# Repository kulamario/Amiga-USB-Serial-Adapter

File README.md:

# Amiga-USB-Serial-Adapter

A simple interface that allows you to connect your Amiga to any PC via a terminal

RS232 and TTL operation possible switched with jumpers

No need drivers just connect via USB to PC

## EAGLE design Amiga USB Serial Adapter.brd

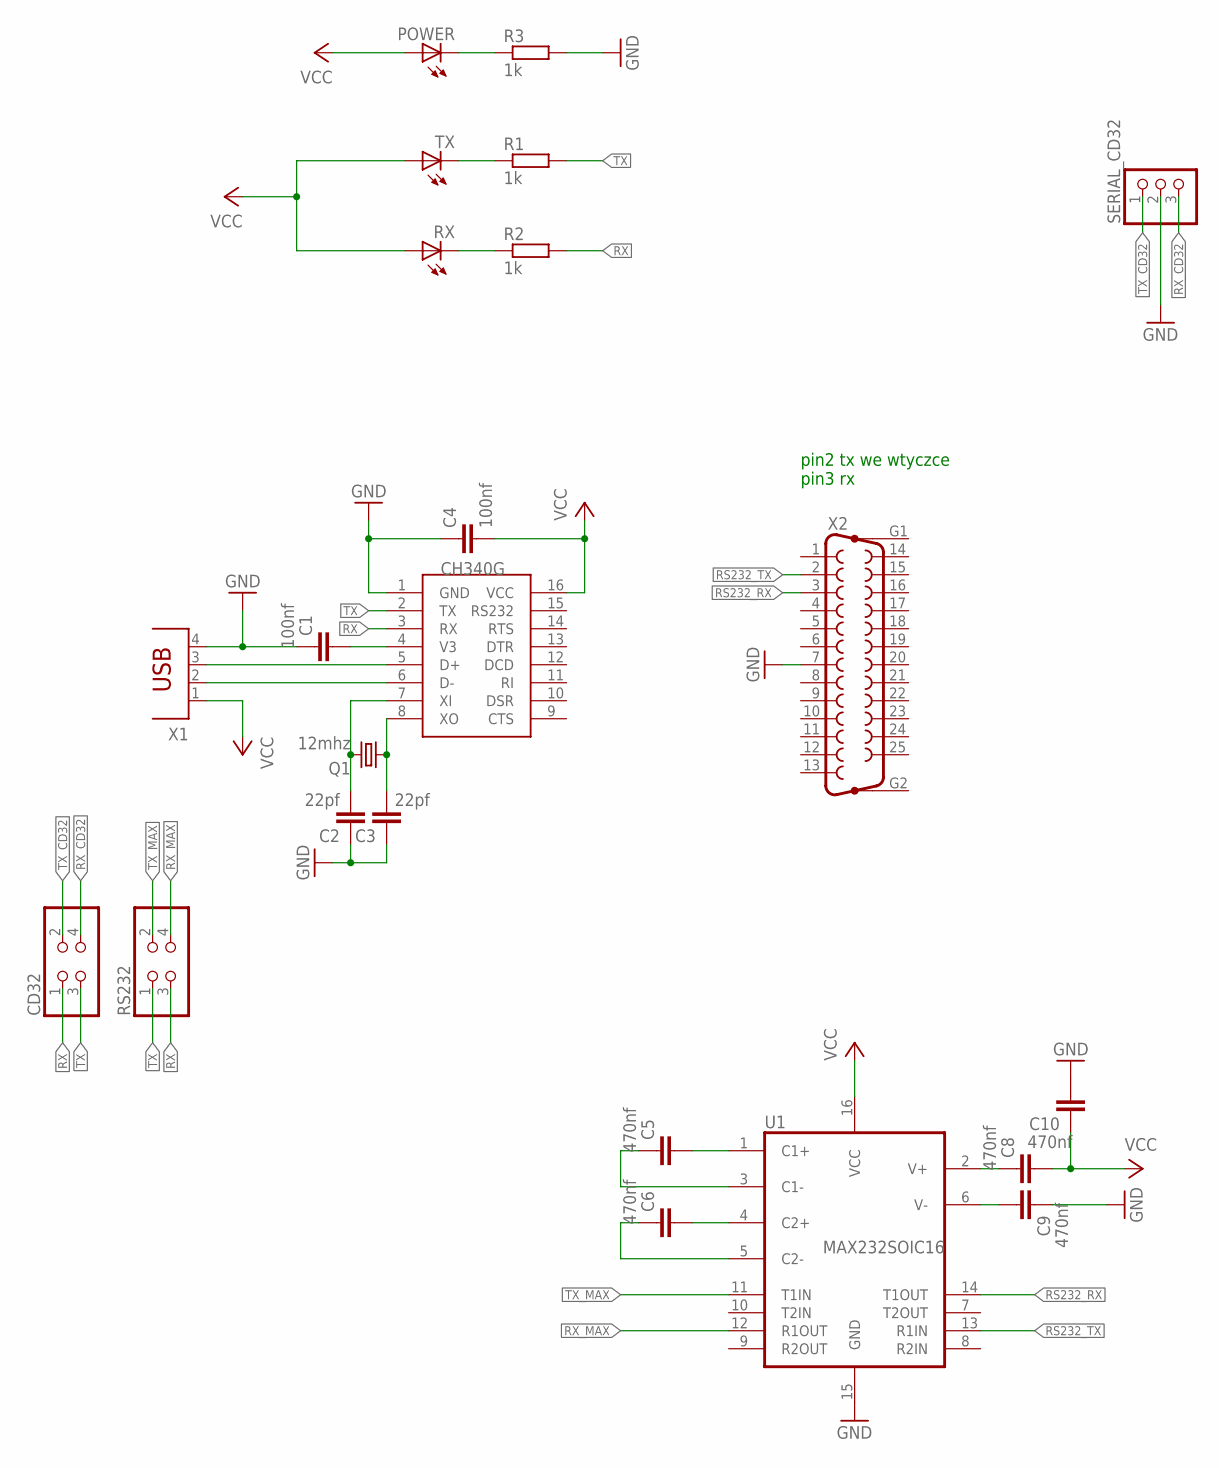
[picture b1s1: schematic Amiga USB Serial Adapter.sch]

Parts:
C1, C4: 100nf; C0805
C2, C3: 22pf; C0805
C5, C6, C8, C9, C10: 470nf; C0805
CD32: PINHD-2X2; 2X02
POWER: LEDCHIPLED_0805; CHIPLED_0805
Q1: 12mhz; HC49U-V
R1, R2, R3: 1k; R0805
RS232: PINHD-2X2; 2X02
RX: LEDCHIPLED_0805; CHIPLED_0805
SERIAL_CD32: PINHD-1X3; 1X03
TX: LEDCHIPLED_0805; CHIPLED_0805
U1: MAX232SOIC16; SO016
U$1: CH340G; SOIC16
X1: PN61729
X2: F25HP

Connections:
GND: C1.1, C2.1, C3.1, C4.1, C9.1, C10.2, R3.2, SERIAL_CD32.2, U1.15 (GND), U$1.1 (GND), X1.4, X2.7
unnamed: U$1.6 (D-), X1.2
unnamed: U$1.5 (D+), X1.3
unnamed: C2.2, Q1.2, U$1.7 (XI)
unnamed: C1.2, U$1.4 (V3)
unnamed: C3.2, Q1.1, U$1.8 (XO)
unnamed: C5.1, U1.3 (C1-)
unnamed: C5.2, U1.1 (C1+)
unnamed: C6.2, U1.4 (C2+)
unnamed: C6.1, U1.5 (C2-)
unnamed: C8.1, U1.2 (V+)
unnamed: C9.2, U1.6 (V-)
unnamed: R1.1, TX.C
unnamed: R2.1, RX.C
unnamed: POWER.C, R3.1
RS232_RX: U1.14 (T1OUT), X2.3
RS232_TX: U1.13 (R1IN), X2.2
RX: CD32.1, R2.2, RS232.3, U$1.3 (RX)
RX_CD32: CD32.4, SERIAL_CD32.3
RX_MAX: RS232.4, U1.12 (R1OUT)
TX: CD32.3, R1.2, RS232.1, U$1.2 (TX)
TX_CD32: CD32.2, SERIAL_CD32.1
TX_MAX: RS232.2, U1.11 (T1IN)
VCC: C4.2, C8.2, C10.1, POWER.A, RX.A, TX.A, U1.16 (VCC), U$1.16 (VCC), X1.1

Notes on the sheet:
pin2 tx we wtyczce pin3 rx

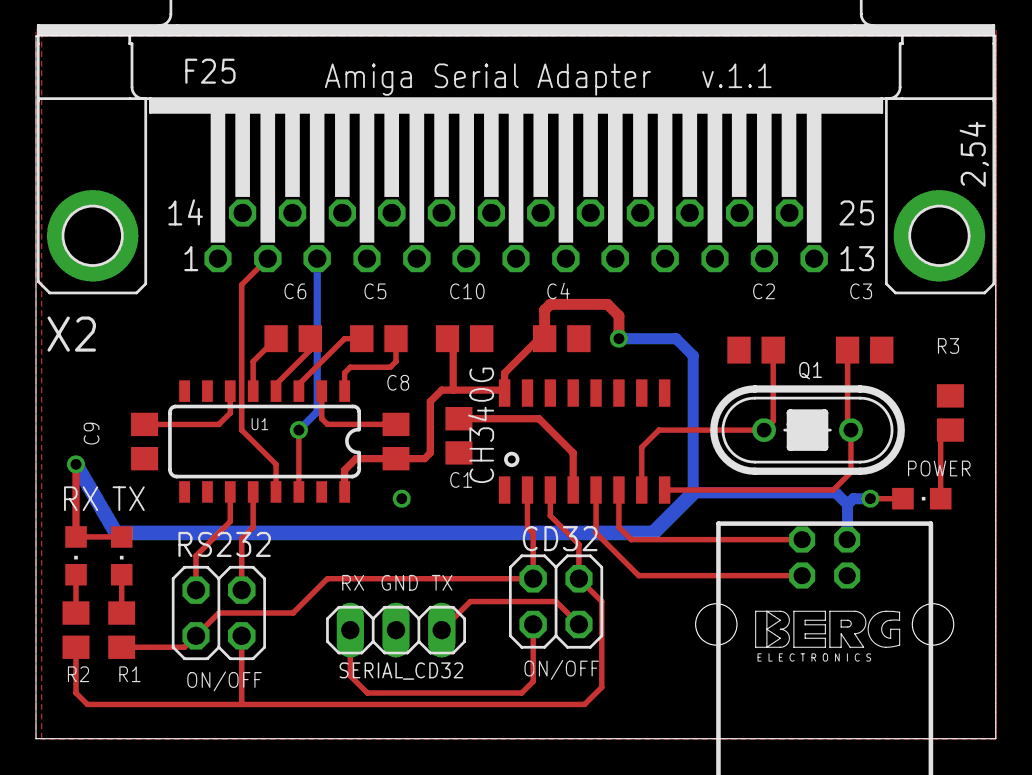
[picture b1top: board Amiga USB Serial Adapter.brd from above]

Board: 2 copper layers, 53.3 x 39.0 mm, 23 parts (0 on the bottom side), 24 nets.

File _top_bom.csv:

Comment,Designator,Footprint,LCSC Part #
1k,R1 R2 R3,R0805,
22pf,C2 C3,C0805,
100nf,C1 C4,C0805,
470nf,C5 C6 C8 C9 C10,C0805,
C601686,TX,C0805,
C98225,RX,C0805,
C440522,POWER ,C0805,
